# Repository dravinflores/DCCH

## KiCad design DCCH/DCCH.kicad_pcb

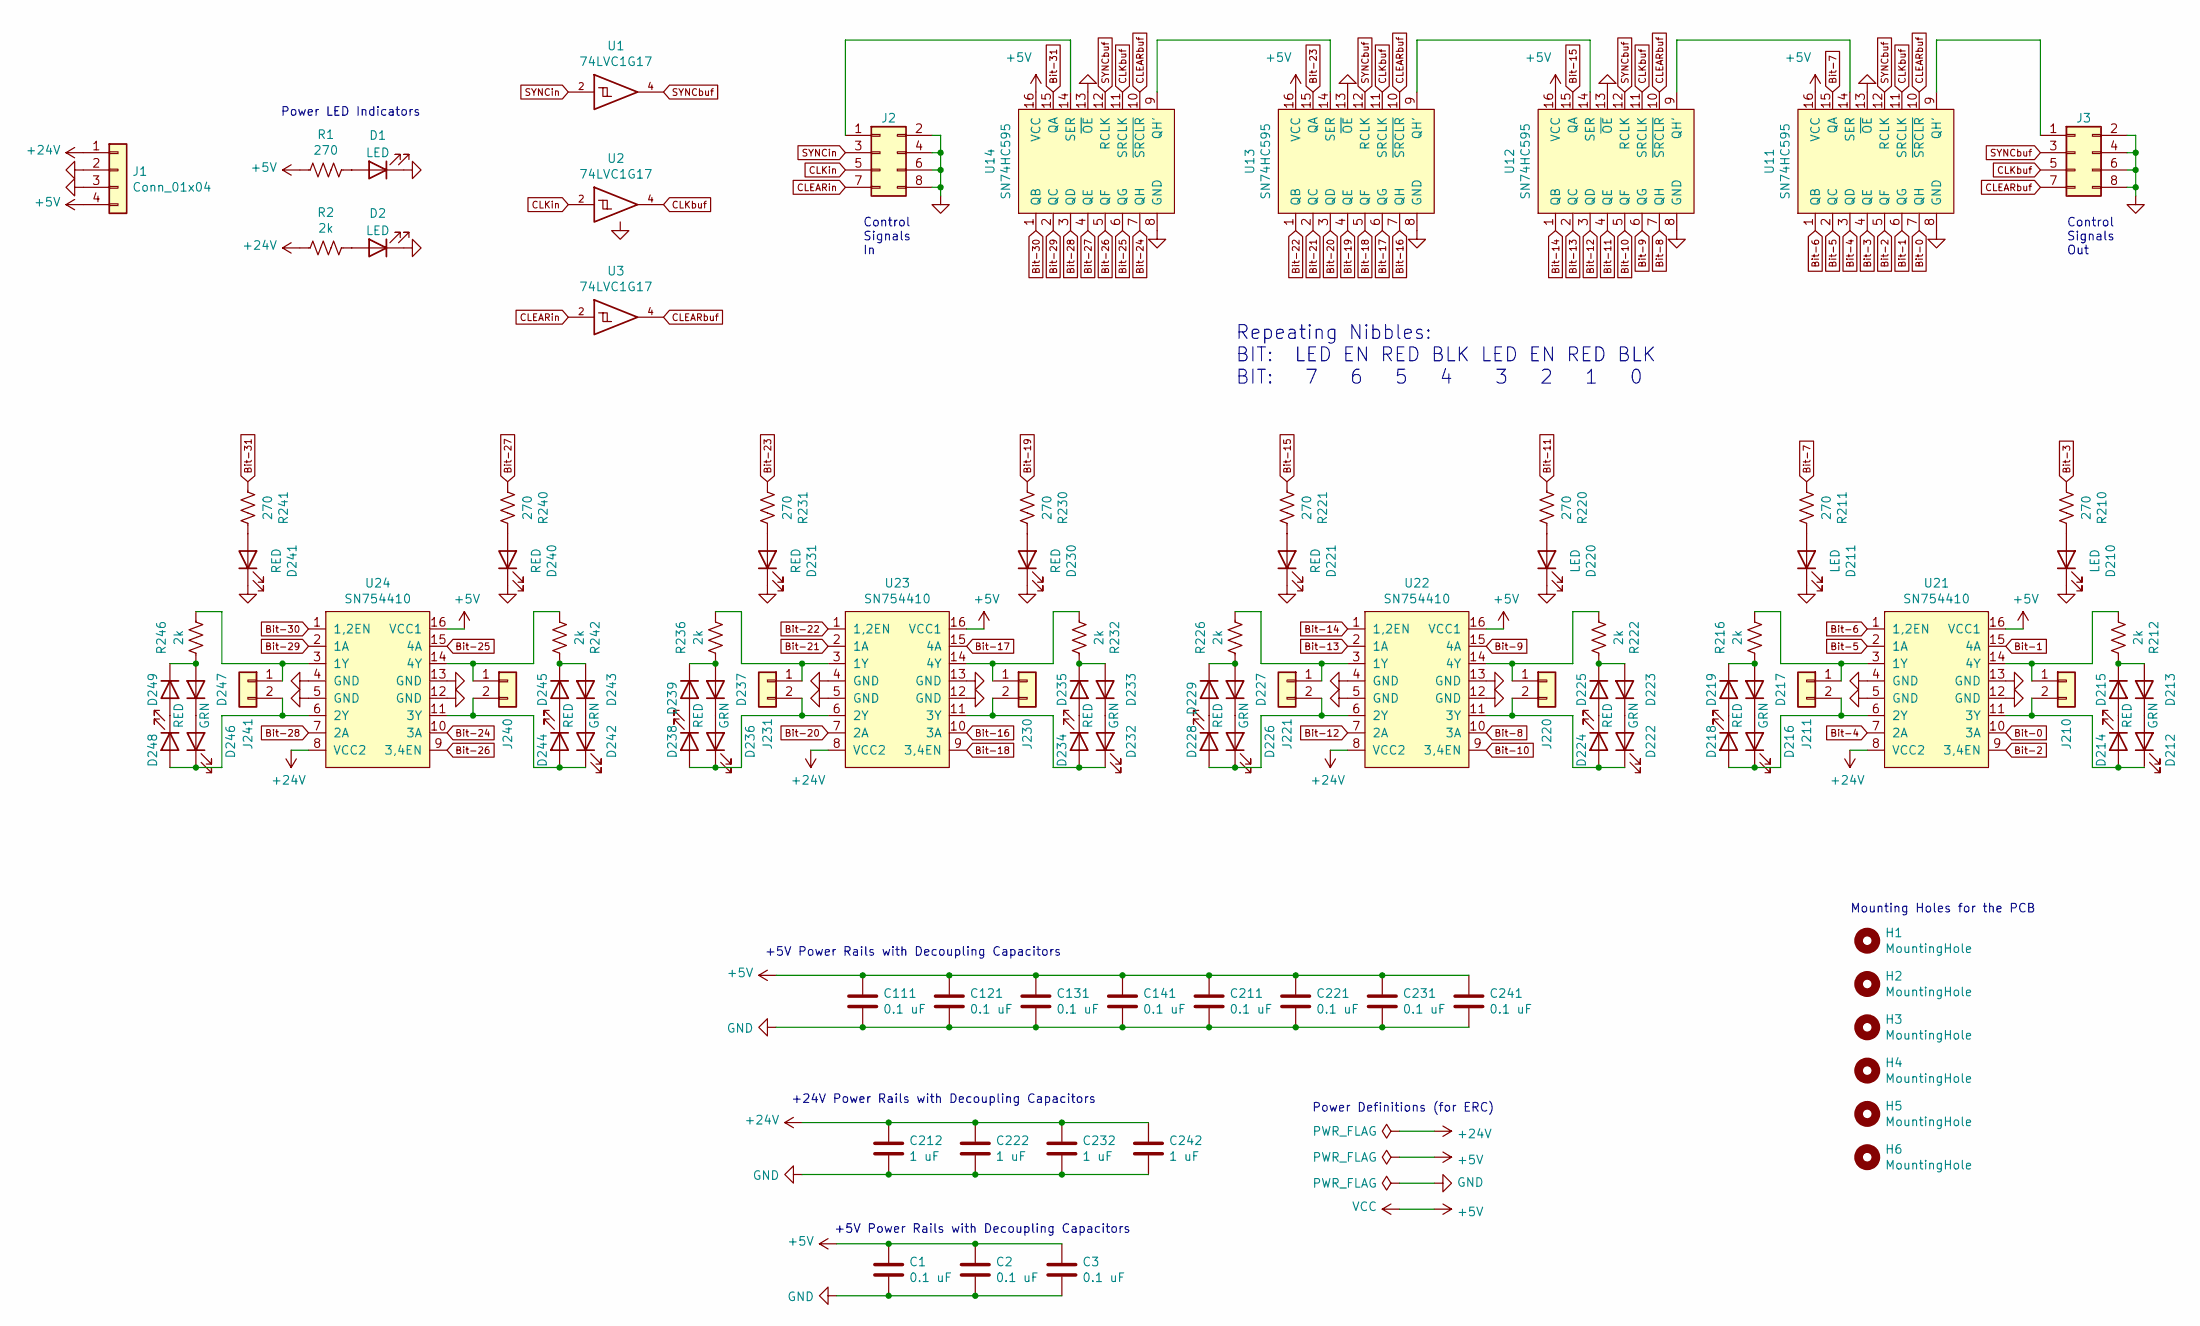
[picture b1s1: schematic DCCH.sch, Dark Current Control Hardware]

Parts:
C1, C2, C3, C111, C121, C131, C141, C211, C221, C231, C241: 0.1 uF; C_0805_2012Metric
C212, C222, C232, C242: 1 uF; C_0805_2012Metric
D1, D2, D210, D211, D220: LED; LED_0805_2012Metric
D212, D216, D222, D226, D232, D236, D242, D246: GRN; LED_0805_2012Metric
D213, D215, D217, D219, D223, D225, D227, D229, D233, D235, D237, D239, D243, D245, D247, D249: 1N4148W; D_SOD-123
D214, D218, D221, D224, D228, D230, D231, D234, D238, D240, D241, D244, D248: RED; LED_0805_2012Metric
H1, H2, H3, H4, H5, H6: MountingHole; MountingHole_3.5mm
J1: Conn_01x04; PhoenixContact_MC_1,5_4-GF-3.5_1x04_P3.50mm_Horizontal_Thre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
J2, J3: Conn_02x04_Odd_Even; IDC-Header_2x04_P2.54mm_Vertical
J210, J211, J220, J221, J230, J231, J240, J241: Conn_01x02; PinHeader_1x02_P2.54mm_Vertical
R1, R210, R211, R220, R221, R230, R231, R240, R241: 270; R_0805_2012Metric
R2, R212, R216, R222, R226, R232, R236, R242, R246: 2k; R_0805_2012Metric
U1, U2, U3: 74LVC1G17; SOT-23-5_HandSoldering
U11, U12, U13, U14: SN74HC595; DIP-16_W7.62mm
U21, U22, U23, U24: SN754410; DIP-16_W7.62mm

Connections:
+5V: C1.1, C2.1, C3.1, C111.1, C121.1, C131.1, C141.1, C211.1, C221.1, C231.1, C241.1, J1.4, R1.2, U1.5 (VCC), U2.5 (VCC), U3.5 (VCC), U11.16 (VCC), U12.16 (VCC), U13.16 (VCC), U14.16 (VCC), U21.16 (VCC1), U22.16 (VCC1), U23.16 (VCC1), U24.16 (VCC1)
+24V: C212.1, C222.1, C232.1, C242.1, J1.1, R2.2, U21.8 (VCC2), U22.8 (VCC2), U23.8 (VCC2), U24.8 (VCC2)
Bit-0: U11.7 (QH), U21.10 (3A)
Bit-1: U11.6 (QG), U21.15 (4A)
Bit-2: U11.5 (QF), U21.9 (3,4EN)
Bit-3: R210.2, U11.4 (QE)
Bit-4: U11.3 (QD), U21.7 (2A)
Bit-5: U11.2 (QC), U21.2 (1A)
Bit-6: U11.1 (QB), U21.1 (1,2EN)
Bit-7: R211.2, U11.15 (QA)
Bit-8: U12.7 (QH), U22.10 (3A)
Bit-9: U12.6 (QG), U22.15 (4A)
Bit-10: U12.5 (QF), U22.9 (3,4EN)
Bit-11: R220.2, U12.4 (QE)
Bit-12: U12.3 (QD), U22.7 (2A)
Bit-13: U12.2 (QC), U22.2 (1A)
Bit-14: U12.1 (QB), U22.1 (1,2EN)
Bit-15: R221.2, U12.15 (QA)
Bit-16: U13.7 (QH), U23.10 (3A)
Bit-17: U13.6 (QG), U23.15 (4A)
Bit-18: U13.5 (QF), U23.9 (3,4EN)
Bit-19: R230.2, U13.4 (QE)
Bit-20: U13.3 (QD), U23.7 (2A)
Bit-21: U13.2 (QC), U23.2 (1A)
Bit-22: U13.1 (QB), U23.1 (1,2EN)
Bit-23: R231.2, U13.15 (QA)
Bit-24: U14.7 (QH), U24.10 (3A)
Bit-25: U14.6 (QG), U24.15 (4A)
Bit-26: U14.5 (QF), U24.9 (3,4EN)
Bit-27: R240.2, U14.4 (QE)
Bit-28: U14.3 (QD), U24.7 (2A)
Bit-29: U14.2 (QC), U24.2 (1A)
Bit-30: U14.1 (QB), U24.1 (1,2EN)
Bit-31: R241.2, U14.15 (QA)
CLEARbuf: J3.7, U3.4, U11.10 (~SRCLR~), U12.10 (~SRCLR~), U13.10 (~SRCLR~), U14.10 (~SRCLR~)
CLEARin: J2.7, U3.2
CLKbuf: J3.5, U2.4, U11.11 (SRCLK), U12.11 (SRCLK), U13.11 (SRCLK), U14.11 (SRCLK)
CLKin: J2.5, U2.2
GND: C1.2, C2.2, C3.2, C111.2, C121.2, C131.2, C141.2, C211.2, C212.2, C221.2, C222.2, C231.2, C232.2, C241.2, C242.2, D1.1 (K), D2.1 (K), D210.1 (K), D211.1 (K), D220.1 (K), D221.1 (K), D230.1 (K), D231.1 (K), D240.1 (K), D241.1 (K), J1.2, J1.3, J2.2, J2.4, J2.6, J2.8, J3.2, J3.4, J3.6, J3.8, U1.3 (GND), U2.3 (GND), U3.3 (GND), U11.8 (GND), U11.13 (~OE~), U12.8 (GND), U12.13 (~OE~), U13.8 (GND), U13.13 (~OE~), U14.8 (GND), U14.13 (~OE~), U21.4 (GND), U21.5 (GND), U21.12 (GND), U21.13 (GND), U22.4 (GND), U22.5 (GND), U22.12 (GND), U22.13 (GND), U23.4 (GND), U23.5 (GND), U23.12 (GND), U23.13 (GND), U24.4 (GND), U24.5 (GND), U24.12 (GND), U24.13 (GND)
unnamed: D1.2 (A), R1.1
unnamed: D2.2 (A), R2.1
unnamed: D210.2 (A), R210.1
unnamed: D211.2 (A), R211.1
unnamed: D212.1 (K), D214.2 (A), J210.2, U21.11 (3Y)
unnamed: D212.2 (A), D213.1 (K)
unnamed: D213.2 (A), D215.1 (K), R212.1
unnamed: D214.1 (K), D215.2 (A)
unnamed: D216.1 (K), D218.2 (A), J211.2, U21.6 (2Y)
unnamed: D216.2 (A), D217.1 (K)
unnamed: D217.2 (A), D219.1 (K), R216.1
unnamed: D218.1 (K), D219.2 (A)
unnamed: D220.2 (A), R220.1
unnamed: D221.2 (A), R221.1
unnamed: D222.1 (K), D224.2 (A), J220.2, U22.11 (3Y)
unnamed: D222.2 (A), D223.1 (K)
unnamed: D223.2 (A), D225.1 (K), R222.1
unnamed: D224.1 (K), D225.2 (A)
unnamed: D226.1 (K), D228.2 (A), J221.2, U22.6 (2Y)
unnamed: D226.2 (A), D227.1 (K)
unnamed: D227.2 (A), D229.1 (K), R226.1
unnamed: D228.1 (K), D229.2 (A)
unnamed: D230.2 (A), R230.1
unnamed: D231.2 (A), R231.1
unnamed: D232.1 (K), D234.2 (A), J230.2, U23.11 (3Y)
unnamed: D232.2 (A), D233.1 (K)
unnamed: D233.2 (A), D235.1 (K), R232.1
unnamed: D234.1 (K), D235.2 (A)
unnamed: D236.1 (K), D238.2 (A), J231.2, U23.6 (2Y)
unnamed: D236.2 (A), D237.1 (K)
unnamed: D237.2 (A), D239.1 (K), R236.1
unnamed: D238.1 (K), D239.2 (A)
unnamed: D240.2 (A), R240.1
unnamed: D241.2 (A), R241.1
unnamed: D242.1 (K), D244.2 (A), J240.2, U24.11 (3Y)
unnamed: D242.2 (A), D243.1 (K)
unnamed: D243.2 (A), D245.1 (K), R242.1
unnamed: D244.1 (K), D245.2 (A)
unnamed: D246.1 (K), D248.2 (A), J241.2, U24.6 (2Y)
unnamed: D246.2 (A), D247.1 (K)
unnamed: D247.2 (A), D249.1 (K), R246.1
unnamed: D248.1 (K), D249.2 (A)
unnamed: J2.1, U14.14 (SER)
unnamed: J3.1, U11.9 (QH')
unnamed: J210.1, R212.2, U21.14 (4Y)
unnamed: J211.1, R216.2, U21.3 (1Y)
unnamed: J220.1, R222.2, U22.14 (4Y)
unnamed: J221.1, R226.2, U22.3 (1Y)
unnamed: J230.1, R232.2, U23.14 (4Y)
unnamed: J231.1, R236.2, U23.3 (1Y)
unnamed: J240.1, R242.2, U24.14 (4Y)
unnamed: J241.1, R246.2, U24.3 (1Y)
unnamed: U11.14 (SER), U12.9 (QH')
unnamed: U12.14 (SER), U13.9 (QH')
unnamed: U13.14 (SER), U14.9 (QH')
SYNCbuf: J3.3, U1.4, U11.12 (RCLK), U12.12 (RCLK), U13.12 (RCLK), U14.12 (RCLK)
SYNCin: J2.3, U1.2

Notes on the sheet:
Control Signals In
Power Definitions (for ERC)
+24V Power Rails with Decoupling Capacitors
+5V Power Rails with Decoupling Capacitors
Mounting Holes for the PCB
Power LED Indicators
Control Signals Out
Repeating Nibbles: BIT: LED EN RED BLK LED EN RED BLK BIT: 7 6 5 4 3 2 1 0

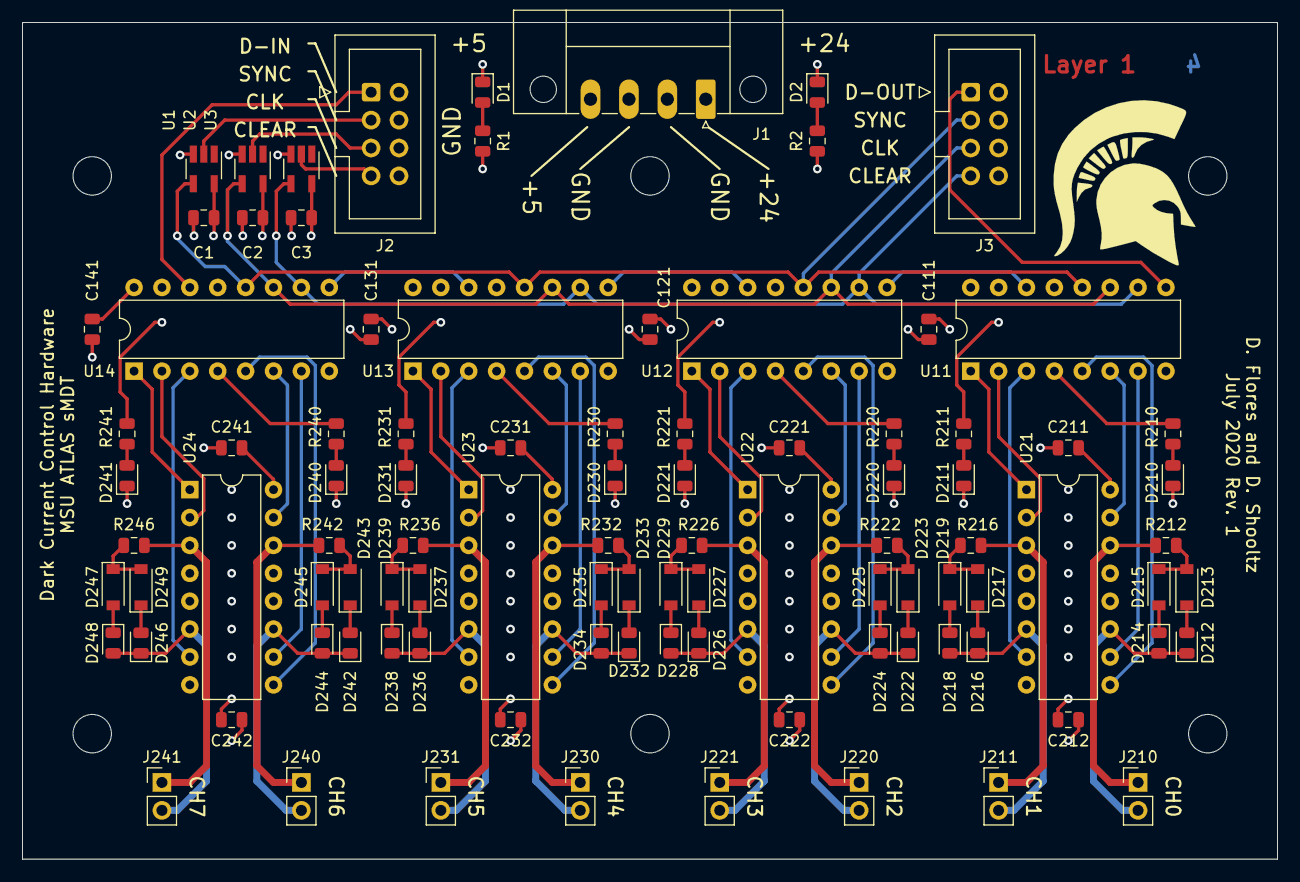
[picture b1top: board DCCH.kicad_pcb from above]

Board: 4 copper layers, 114.3 x 76.2 mm, 103 parts (0 on the bottom side), 96 nets.

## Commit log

2020-06-25 Initial Commit.
2020-06-25 Added the Plots folder, as well as removed the readme in the DCCH folder, seeing as it was useless.
2020-06-25 Removed DS_STORE file
2020-06-26 Updated schematic. One shift register to one h-bridge. Also put in resistors for unused outputs.
2020-06-26 Added updated plots.
2020-06-26 Updated plots once again.
2020-06-26 Rewired everything. Removed the resistors. Now the control bit pattern for the shift registers makes sense.
2020-06-26 Also added new 3D renders.
2020-06-26 Fixed the plots.
2020-06-29 Removed the vias from the power connectors.
2020-06-29 Removed power traces and vias. Power plane connects these nets automatically.
2020-06-29 Updated measurements for PCB outline.
2020-06-29 Added a layer number indicator.
2020-06-29 Fixed WRITE and SYNC pins, as they were mixed up.
2020-06-29 Added a small python program to illustrate the operation of a shift register.
2020-06-30 Updated Python program for readability, as well as accuracy.
2020-06-30 Fixed ground plane.
2020-07-18 Changed board layout once again. Updated schematic. Updated board.
2020-07-18 Added plots and fixed silk screen.
2020-07-18 Fixed render as well as plots.
2020-07-26 Changed orientation again.
2020-07-26 Updated silksceen as well as plots.
2020-08-04 Dean completely overhauled the board. Updated board and schematics
2020-08-04 Updated plots.
